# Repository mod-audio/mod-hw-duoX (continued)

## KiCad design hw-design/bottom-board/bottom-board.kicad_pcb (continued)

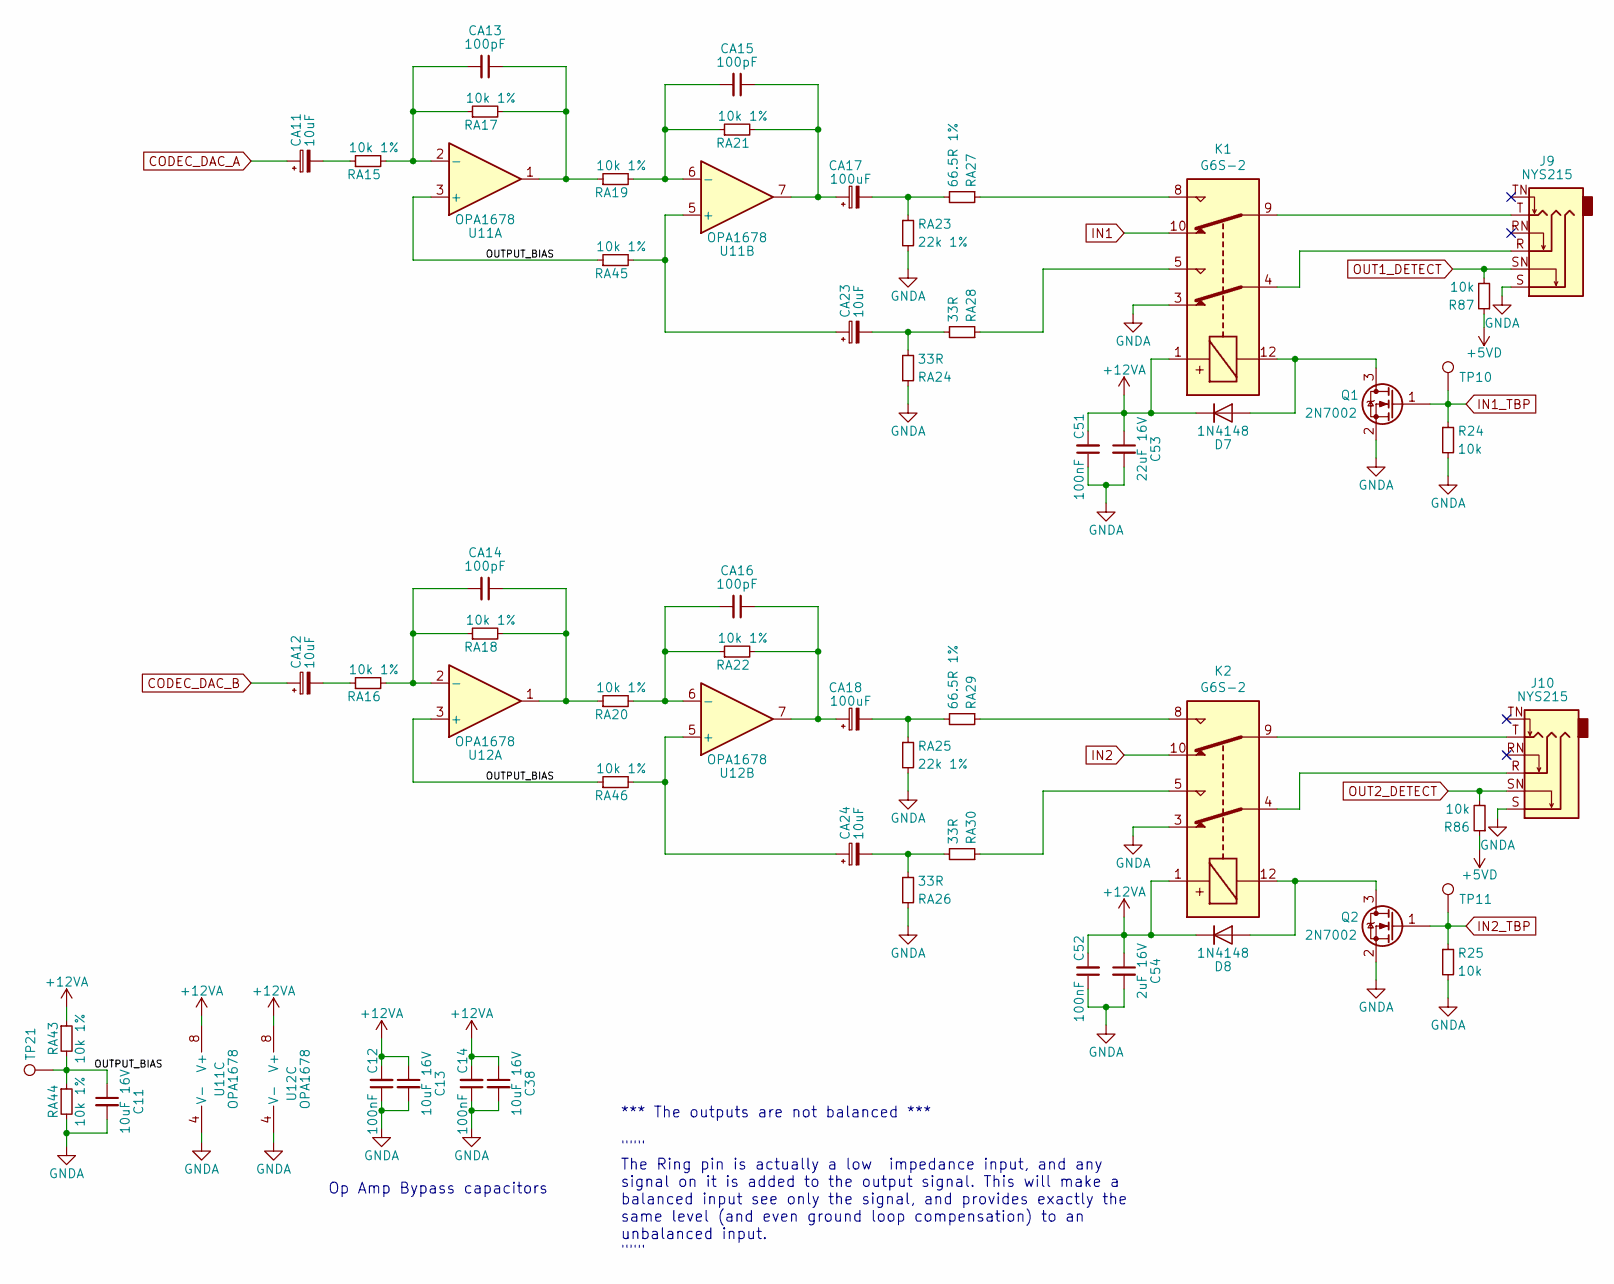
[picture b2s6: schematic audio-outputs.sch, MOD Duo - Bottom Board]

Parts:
C11, C13, C38: 10uF 16V; C_0805_2012Metric; MPN CL21A106KOFNNNE
C12, C14, C51, C52: 100nF; C_0603_1608Metric; MPN GCM188R71C104KA37D
C53: 22uF 16V; C_0805_2012Metric; MPN GRM21BC81C226ME44L
C54: 2uF 16V; C_0805_2012Metric; MPN GRM21BC81C226ME44L
CA11, CA12, CA23, CA24: 10uF; CP_Elec_4x5.7; MPN EEE-HB1C100R
CA13, CA14, CA15, CA16: 100pF; C_0603_1608Metric; MPN C0603C101J3GACTU
CA17, CA18: 100uF; CP_Elec_6.3x7.7; MPN UWX1C101MCL1GB
D7, D8: 1N4148; D_SOD-323; MPN 1N4148WX-TP
J9, J10: NYS215; NMJ6HCD2; MPN NYS215
K1, K2: G6S-2; Relay_DPDT_Omron_G6S-2F; MPN EE2-12NU-L
Q1, Q2: 2N7002; SOT-23; MPN 2N7002P,215
R24, R25, R86, R87: 10k; R_0603_1608Metric; MPN RMCF0603JT10K0
RA15, RA16, RA17, RA18, RA19, RA20, RA21, RA22, RA43, RA44, RA45, RA46: 10k 1%; R_0603_1608Metric; MPN RR0816P-103-D
RA23, RA25: 22k 1%; R_0603_1608Metric; MPN RR0816P-223-D
RA24, RA26, RA28, RA30: 33R; R_0603_1608Metric; MPN RT0603DRE0733RL
RA27, RA29: 66.5R 1%; R_0603_1608Metric; MPN RR0816Q-66R5-D-80R
TP10, TP11, TP21: TestPoint; TestPoint_Pad_D1.0mm
U11, U12: OPA1678; SOIC-8_3.9x4.9mm_P1.27mm; MPN OPA1678IDR

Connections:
+5VD: R86.1, R87.1; also elsewhere on the board
+12VA: C12.2, C13.1, C14.2, C38.1, C51.2, C52.2, C53.1, C54.1, D7.1 (K), D8.1 (K), K1.1, K2.1, RA43.1, U11.8 (V+), U12.8 (V+); also elsewhere on the board
/audio-outputs/OUTPUT_BIAS: C11.1, RA43.2, RA44.1, RA45.1, RA46.1, TP21.1, U11.3 (+), U12.3 (+)
CODEC_DAC_A: CA11.1; also elsewhere on the board
CODEC_DAC_B: CA12.1; also elsewhere on the board
IN1: K1.10; also elsewhere on the board
IN1_TBP: Q1.1 (G), R24.1, TP10.1; also elsewhere on the board
IN2: K2.10; also elsewhere on the board
IN2_TBP: Q2.1 (G), R25.1, TP11.1; also elsewhere on the board
unnamed: CA11.2, RA15.1
unnamed: CA12.2, RA16.1
unnamed: CA13.1, RA17.2, RA19.1, U11.1
unnamed: CA13.2, RA15.2, RA17.1, U11.2 (-)
unnamed: CA14.1, RA18.2, RA20.1, U12.1
unnamed: CA14.2, RA16.2, RA18.1, U12.2 (-)
unnamed: CA15.1, CA17.1, RA21.2, U11.7
unnamed: CA15.2, RA19.2, RA21.1, U11.6 (-)
unnamed: CA16.1, CA18.1, RA22.2, U12.7
unnamed: CA16.2, RA20.2, RA22.1, U12.6 (-)
unnamed: CA17.2, RA23.1, RA27.2
unnamed: CA18.2, RA25.1, RA29.2
unnamed: CA23.1, RA45.2, U11.5 (+)
unnamed: CA23.2, RA24.2, RA28.2
unnamed: CA24.1, RA46.2, U12.5 (+)
unnamed: CA24.2, RA26.2, RA30.2
unnamed: D7.2 (A), K1.12, Q1.3 (D)
unnamed: D8.2 (A), K2.12, Q2.3 (D)
unnamed: J9.R, K1.4
unnamed: J9.T, K1.9
unnamed: J10.R, K2.4
unnamed: J10.T, K2.9
unnamed: K1.5, RA28.1
unnamed: K1.8, RA27.1
unnamed: K2.5, RA30.1
unnamed: K2.8, RA29.1
OUT1_DETECT: J9.SN, R87.2; also elsewhere on the board
OUT2_DETECT: J10.SN, R86.2; also elsewhere on the board

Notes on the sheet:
*** The outputs are not balanced *** """ The Ring pin is actually a low impedance input, and any signal on it is added to the output signal. This will make a balanced input see only the signal, and provides exactly the same level (and even ground loop compensation) to an unbalanced input. """
Op Amp Bypass capacitors

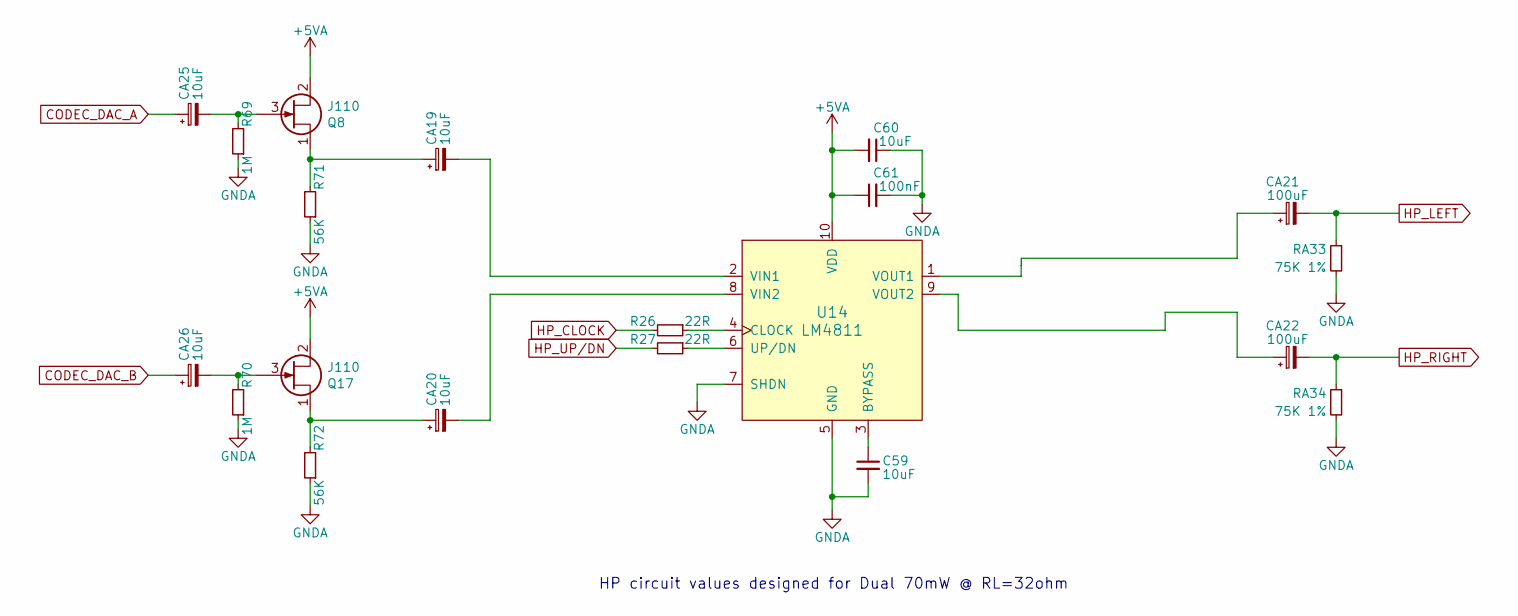
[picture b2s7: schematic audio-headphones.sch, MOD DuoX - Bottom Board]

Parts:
C59, C60: 10uF; C_0603_1608Metric; MPN CL10A106MQ8NNNC
C61: 100nF; C_0603_1608Metric; MPN GCM188R71C104KA37D
CA19, CA20, CA25, CA26: 10uF; CP_Elec_4x5.7; MPN EEE-HB1C100R
CA21, CA22: 100uF; CP_Elec_6.3x7.7; MPN UWX1C101MCL1GB
Q8, Q17: J110; SOT-23; MPN PMBFJ110,215
R26, R27: 22R; R_0603_1608Metric; MPN RMCF0603JT22R0
R69, R70: 1M; R_0603_1608Metric; MPN RT0603BRD071ML
R71, R72: 56K; R_0603_1608Metric; MPN RMCF0603FT56K0
RA33, RA34: 75K 1%; R_0603_1608Metric; MPN RR0816P-753-D
U14: LM4811; MSOP-10_3x3mm_P0.5mm; MPN LM4811MM/NOPB

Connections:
CODEC_DAC_A: CA25.1; also elsewhere on the board
CODEC_DAC_B: CA26.1; also elsewhere on the board
HP_CLOCK: R26.2; also elsewhere on the board
HP_LEFT: CA21.2, RA33.1; also elsewhere on the board
HP_RIGHT: CA22.2, RA34.1; also elsewhere on the board
HP_UP/DN: R27.2; also elsewhere on the board
unnamed: C59.1, U14.3 (BYPASS)
unnamed: CA19.1, Q8.1 (D), R71.2
unnamed: CA19.2, U14.2 (VIN1)
unnamed: CA20.1, Q17.1 (D), R72.2
unnamed: CA20.2, U14.8 (VIN2)
unnamed: CA21.1, U14.1 (VOUT1)
unnamed: CA22.1, U14.9 (VOUT2)
unnamed: CA25.2, Q8.3 (G), R69.2
unnamed: CA26.2, Q17.3 (G), R70.2
unnamed: R26.1, U14.4 (CLOCK)
unnamed: R27.1, U14.6 (UP/DN)

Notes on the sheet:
HP circuit values designed for Dual 70mW @ RL=32ohm

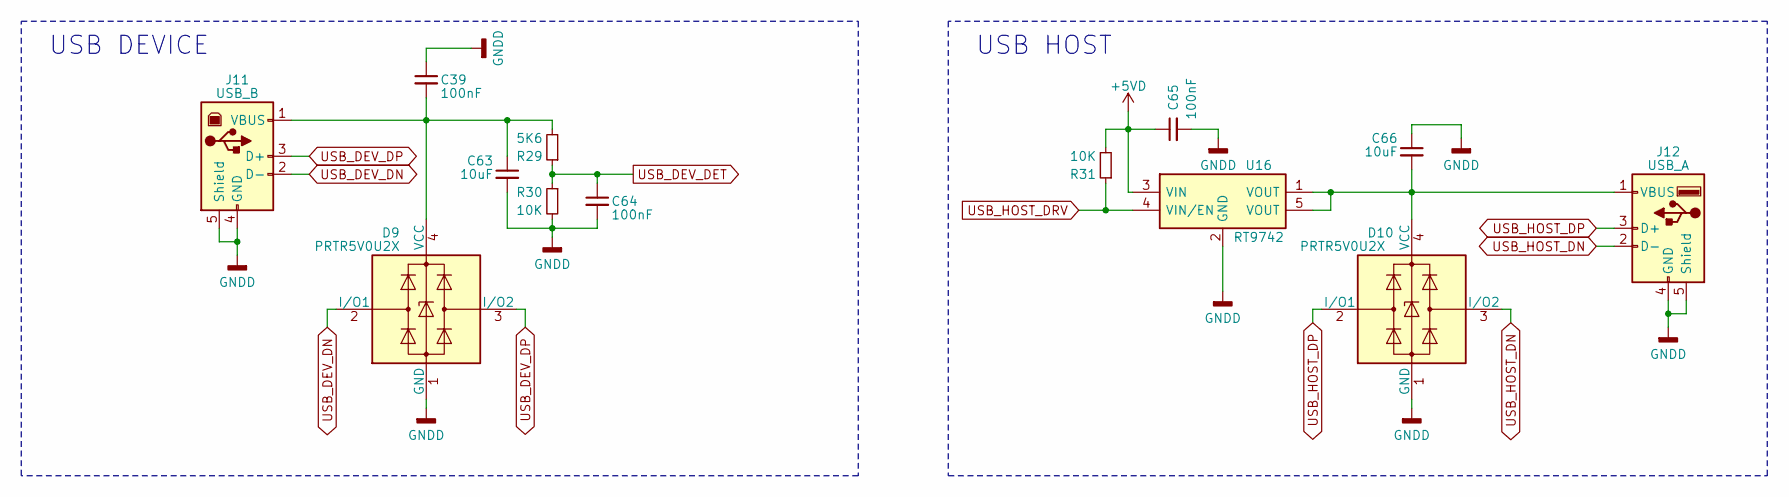
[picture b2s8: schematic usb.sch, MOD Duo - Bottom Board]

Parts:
C39, C64, C65: 100nF; C_0603_1608Metric; MPN GCM188R71C104KA37D
C63, C66: 10uF; C_0603_1608Metric; MPN CL10A106MQ8NNNC
D9, D10: PRTR5V0U2X; SOT-143; MPN PRTR5V0U2X,215
J11: USB_B; USB_B_OST_USB-B1HSxx_Horizontal; MPN 61729-1011BLF
J12: USB_A; USB_A_Vertical; MPN 73725-0110BLF
R29: 5K6; R_0603_1608Metric; MPN ERA-3AEB5621V
R30, R31: 10K; R_0603_1608Metric; MPN RR0816P-103-D
U16: RT9742; TSOT-23-5; MPN RT9742MNGJ5

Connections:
+5VD: C65.1, R31.2, U16.3 (VIN); also elsewhere on the board
unnamed: C39.2, C63.1, D9.4 (VCC), J11.1 (VBUS), R29.2
unnamed: C66.2, D10.4 (VCC), J12.1 (VBUS), U16.1 (VOUT), U16.5 (VOUT)
USB_DEV_DET: C64.1, R29.1, R30.1; also elsewhere on the board
USB_DEV_DN: D9.2 (I/O1), J11.2 (D-); also elsewhere on the board
USB_DEV_DP: D9.3 (I/O2), J11.3 (D+); also elsewhere on the board
USB_HOST_DN: D10.3 (I/O2), J12.2 (D-); also elsewhere on the board
USB_HOST_DP: D10.2 (I/O1), J12.3 (D+); also elsewhere on the board
USB_HOST_DRV: R31.1, U16.4 (VIN/EN); also elsewhere on the board

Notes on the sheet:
USB DEVICE
USB HOST

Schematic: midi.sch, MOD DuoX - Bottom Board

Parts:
D11, D12: 1N4148; D_SOD-323; MPN 1N4148WX-TP
J13, J14: DIN_5; SDS-50J; MPN SDS-50J
Q3, Q4: 2N7002; SOT-23; MPN 2N7002P,215
R32, R33, R34: 220R; R_0603_1608Metric; MPN ESR03EZPJ221
R35, R36: 10K; R_0603_1608Metric; MPN RR0816P-103-D
U17: 6N136S; SMDIP-8_W9.53mm; MPN 6N136S

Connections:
+5VD: R33.2, R35.1, R36.1, U17.8; also elsewhere on the board
CLI_UART_RX: J14.3; also elsewhere on the board
CLI_UART_TX: J14.1; also elsewhere on the board
MIDI_UART_RX: D12.2 (A); also elsewhere on the board
MIDI_UART_TX: Q4.1 (G); also elsewhere on the board
unnamed: D11.1 (K), R32.2, U17.2
unnamed: D11.2 (A), J13.5, U17.3
unnamed: D12.1 (K), U17.6
unnamed: J13.4, R32.1
unnamed: J14.4, R33.1
unnamed: J14.5, R34.1
unnamed: Q3.1 (G), Q4.3 (D), R36.2
unnamed: Q3.3 (D), R34.2, R35.2

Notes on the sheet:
MIDI IN
MIDI OUT
MIDI Out connector exposes the debug serial.
Opto: If = 16mA, Vf = 1.4V
MIDI In connector can be used to trigger a special boot mode by connecting pin 3 to GND.

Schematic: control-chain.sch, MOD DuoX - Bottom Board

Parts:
C67, C68: 10uF; C_0603_1608Metric; MPN CL10A106MQ8NNNC
C69: 10uF 16V; C_0805_2012Metric; MPN CL21A106KOFNNNE
C70, C71: 100nF; C_0603_1608Metric; MPN GCM188R71C104KA37D
J15: RJHSE-5381; RJ45_Amphenol_RJHSE538X; MPN RJHSE-5381
Q5, Q6: BSS84; SOT-23; MPN BSS84-7-F
R37, R38: 22R; R_0603_1608Metric; MPN RMCF0603JT22R0
R39, R40: 10K; R_0603_1608Metric; MPN RR0816P-103-D
R41, R42: 220R; R_0603_1608Metric; MPN ESR03EZPJ221
R43, R44, R45, R46: 56R; R_0603_1608Metric; MPN RMCF0603JT56R0
R47: 100R; R_0603_1608Metric; MPN RR0816P-101-D
U18: ISL83086E; SOIC-14_3.9x8.7mm_P1.27mm; MPN ISL83086EIBZ

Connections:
+5VD: C71.1, Q5.2 (S), Q6.2 (S), R39.1, U18.13 (VCC), U18.14 (VCC); also elsewhere on the board
+12V: C69.1, C70.1, J15.4, J15.5; also elsewhere on the board
CHAIN_UART_DE: R40.1, U18.4 (DE); also elsewhere on the board
CHAIN_UART_RE: R39.2, U18.3 (~RE); also elsewhere on the board
CHAIN_UART_RX: Q6.1 (G), R38.1; also elsewhere on the board
CHAIN_UART_TX: R37.1; also elsewhere on the board
unnamed: J15.10, R42.1
unnamed: J15.12, R41.1
unnamed: Q5.1 (G), R37.2, U18.5 (DI)
unnamed: R38.2, U18.2 (RO)
unnamed: R43.2, U18.12 (A)
unnamed: R44.2, U18.11 (~B)
unnamed: R45.2, U18.9 (Y)
unnamed: R46.2, U18.10 (~Z~)
RS485_RX+: J15.3, R43.1, R47.1
RS485_RX-: J15.6, R44.1, R47.2
RS485_RX_LED: C68.1, Q6.3 (D), R41.2
RS485_TX+: J15.1, R45.1
RS485_TX-: J15.2, R46.1
RS485_TX_LED: C67.1, Q5.3 (D), R42.2

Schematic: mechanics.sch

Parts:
FID1, FID2, FID3: FIDUCIAL; fiducial_in-circuit
H1, H2, H3, H4, H5: HOLE; Hole_3.5mm
H6, H7: Standoff; 9774027151R; MPN 9774027151R
IMG1: Logo; mod-logo

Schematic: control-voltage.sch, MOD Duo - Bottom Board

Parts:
C34: 10uF 16V; C_0805_2012Metric; MPN CL21A106KOFNNNE
C35, C76, C81: 10uF; C_0603_1608Metric; MPN CL10A106MQ8NNNC
C73, C74: 33nF; C_0603_1608Metric; MPN C0603C333K4RACTU
C75, C80, C82, C83: 100nF; C_0603_1608Metric; MPN GCM188R71C104KA37D
C77: 1uF; C_0603_1608Metric; MPN CL10B105KP8NNNC
D13, D20: 1N4148WS-Diode; D_SOD-323
D14, D15: BAT54S; SOT-23; MPN BAT54SFILM
J16, J17: NYS215; NMJ6HCD2; MPN NYS215
R17, R48, R50, R51, R52, R79, R80, R82: 10K; R_0603_1608Metric; MPN RR0816P-103-D
RA31, RA32, RA35, RA36, RA47, RA48, RA51, RA52: 10K 1%; R_0603_1608Metric; MPN RR0816P-103-D
RA49, RA50: 499k 1%; R_0603_1608Metric; MPN ERJ-3EKF4993V
RA53, RA54: 1K 1%; R_0603_1608Metric; MPN CR0603-FX-3012ELF
TP14, TP15, TP16: TestPoint; TestPoint_Pad_D1.0mm
U4: LD1117S50TR_SOT223; SOT-223-3_TabPin2; MPN LD1117S50TR
U9, U13: DG9426E; TSSOP-16_4.4x5mm_P0.65mm
U10: LM358; TSSOP-8_3x3mm_P0.65mm; MPN LM358DGKR
U20: ADC122S021; VSSOP-8_3.0x3.0mm_P0.65mm; MPN ADC122S021CIMM/NOPB
U21: MIC2076A; SOIC-8_3.9x4.9mm_P1.27mm; MPN MIC2076A-1YM
U22: 74LVC3G17; VSSOP-8_2.3x2mm_P0.5mm; MPN SN74LVC3G17DCUR
U24: MCP4922-EP; SOIC-14_3.9x8.7mm_P1.27mm; MPN MCP4922T-E/SL

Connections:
+5VP: C35.1, C75.2, C76.1, C77.2, D14.2, D15.2, R82.1, U4.2 (VO), U9.12 (VL), U20.2 (VA), U21.7 (IN)
+12VA: C34.1, U4.3 (VI), U9.13 (V+), U10.8 (V+), U13.13 (V+); also elsewhere on the board
CV_10V_OUT1: RA51.2, U10.1, U13.11
CV_10V_OUT2: RA52.2, U10.7, U13.15
CV_ADC_DIN: U20.6 (DIN); also elsewhere on the board
CV_ADC_DOUT: U20.7 (DOUT); also elsewhere on the board
CV_ADC_SCLK: U20.8 (SCLK); also elsewhere on the board
CV_ADC_~CS~: TP16.1, U20.1 (~CS~); also elsewhere on the board
CV_DAC_SCK: U22.3; also elsewhere on the board
CV_DAC_SDI: U22.1; also elsewhere on the board
CV_DAC_~CS~: U22.6; also elsewhere on the board
CV_EXP_SW: D13.1 (K), D20.1 (K), R48.1, U9.1, U9.8, U9.9, U9.16
CV_IN_DET: J16.SN, R82.2; also elsewhere on the board
CV_OUT_1: RA53.2, U10.3 (+)
CV_OUT_2: RA54.2, U10.5 (+)
CV_OUT_DET: J17.SN, R17.2; also elsewhere on the board
EXP_FLAG1: R80.1, U21.2 (FLGA); also elsewhere on the board
EXP_FLAG2: R79.1, U21.3 (FLGB); also elsewhere on the board
HP_CV_JACK_RING: J17.R, U13.6, U13.14
HP_CV_JACK_TIP: J17.T, U13.3, U13.10
HP_DISABLE: R52.1, U13.1, U13.8, U13.9, U13.16; also elsewhere on the board
HP_LEFT: U13.2; also elsewhere on the board
HP_RIGHT: U13.7; also elsewhere on the board
unnamed: C73.1, D15.3, U9.2, U9.15, U20.5 (IN1)
unnamed: C74.1, D14.3, U9.7, U9.10, U20.4 (IN2)
unnamed: RA31.2, RA32.1, U9.6
unnamed: RA35.2, RA36.1, U9.3
unnamed: RA47.2, RA51.1, U10.2 (-)
unnamed: RA48.2, RA52.1, U10.6 (-)
unnamed: RA49.2, RA53.1, U24.14 (VoutA)
unnamed: RA50.2, RA54.1, U24.10 (VoutB)
unnamed: U22.2, U24.3 (~CS~)
unnamed: U22.5, U24.4 (SCK)
unnamed: U22.7, U24.5 (SDI)

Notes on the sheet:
CV INPUT
CV OUTPUT
Exp. Pedal Enable
MIC2076A outputs have Hi-Z when disabled
DAC outputs have Hi-Z (500k) when shutdown is on
Amplify the signel by a factor of 2, to scale back to the 0 to 10V range

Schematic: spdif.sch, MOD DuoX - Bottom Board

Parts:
C84: 10nF; C_0603_1608Metric; MPN CL10B103KA8NNNC
C85: 22pF; C_0603_1608Metric; MPN C0603C220K4GACTU
J18: MJ-3536N; MPN MJ-3536N
R55: 243R; R_0603_1608Metric; MPN RC0603FR-07243RL
R56: 107R; R_0603_1608Metric; MPN RC0603FR-07107RL
TR1: Transformer_1P_1S_SO8; PE-65812NL; MPN PE-65812NL

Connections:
CODEC_SPDIF_OUT: C84.2; also elsewhere on the board
unnamed: C84.1, R55.2
unnamed: C85.2, J18.S, TR1.5 (SA)
unnamed: J18.T, TR1.8 (SB)
unnamed: R55.1, R56.1, TR1.1 (AA)

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
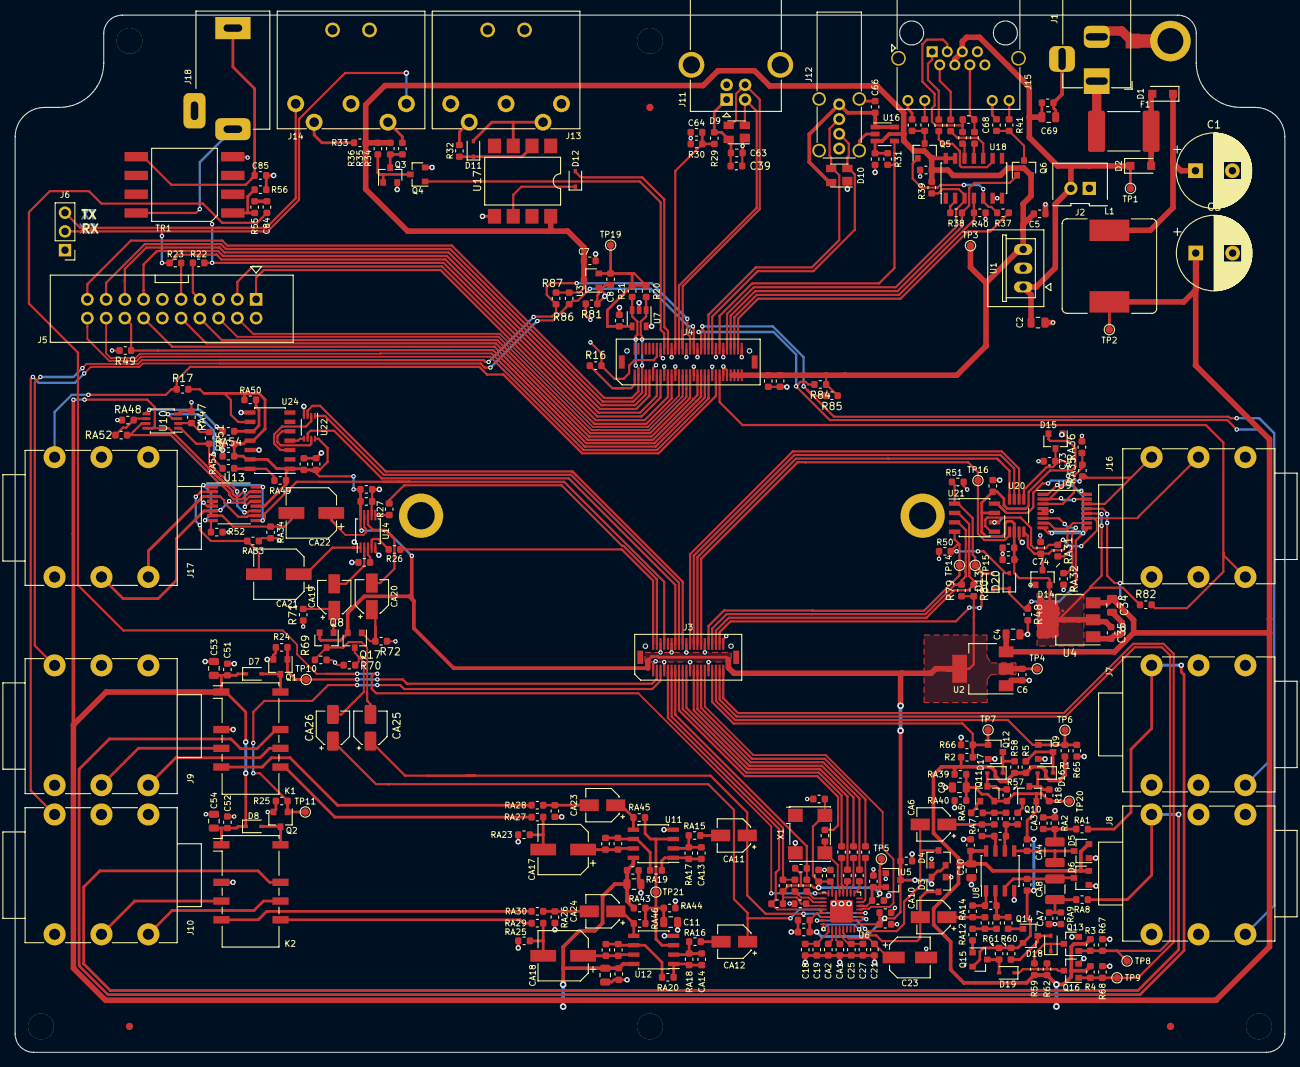
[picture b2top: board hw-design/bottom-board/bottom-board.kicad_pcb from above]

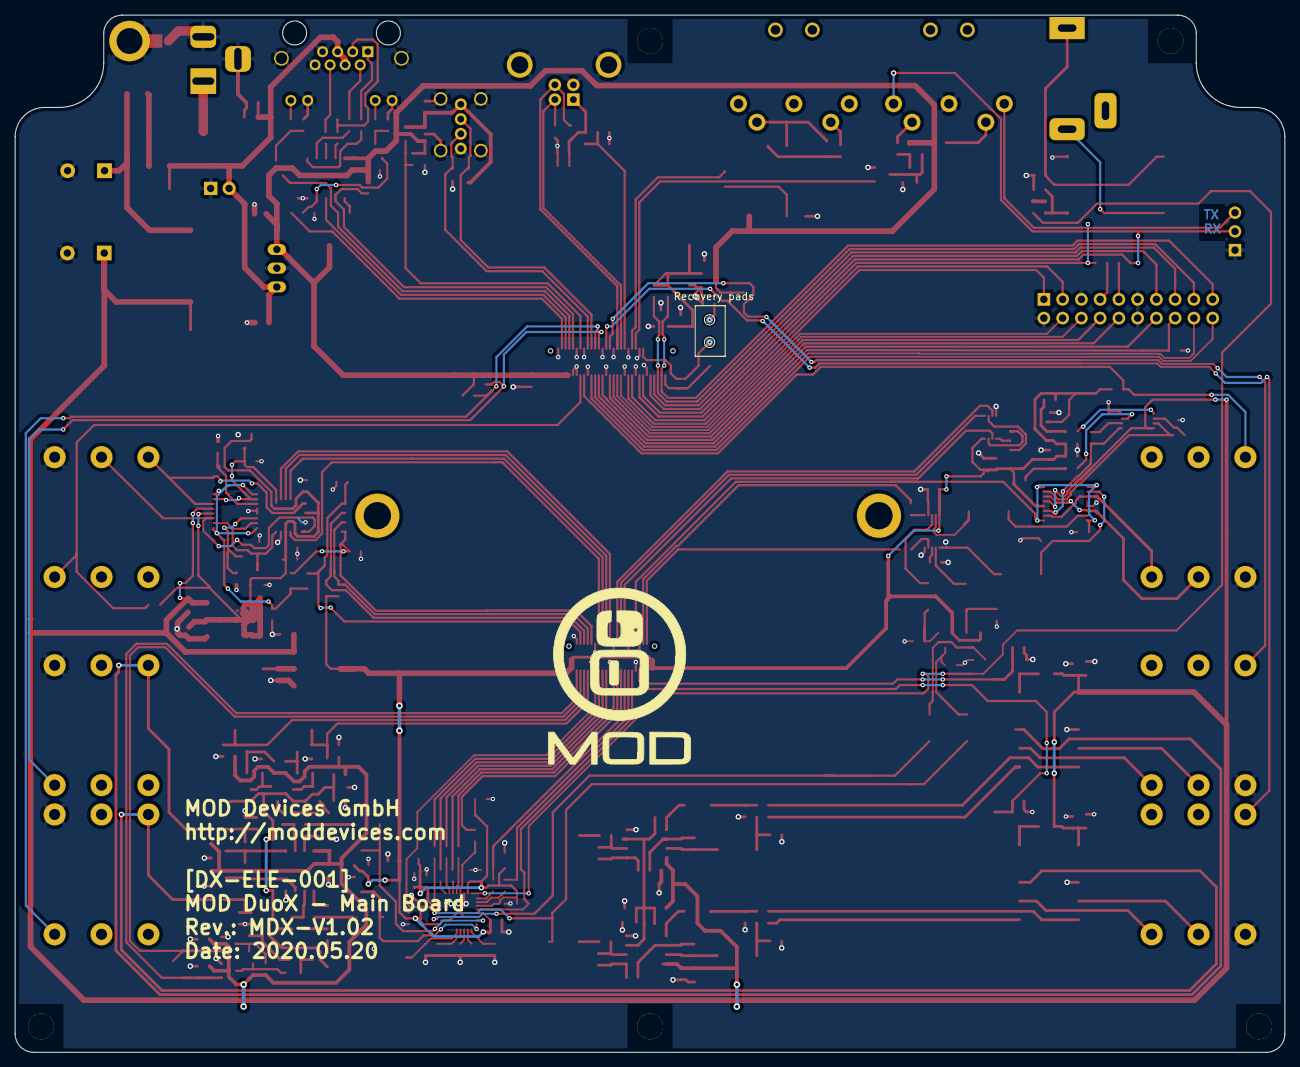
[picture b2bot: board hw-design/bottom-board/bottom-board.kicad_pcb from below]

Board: 2 copper layers, 172.0 x 140.5 mm, 331 parts (3 on the bottom side), 213 nets.

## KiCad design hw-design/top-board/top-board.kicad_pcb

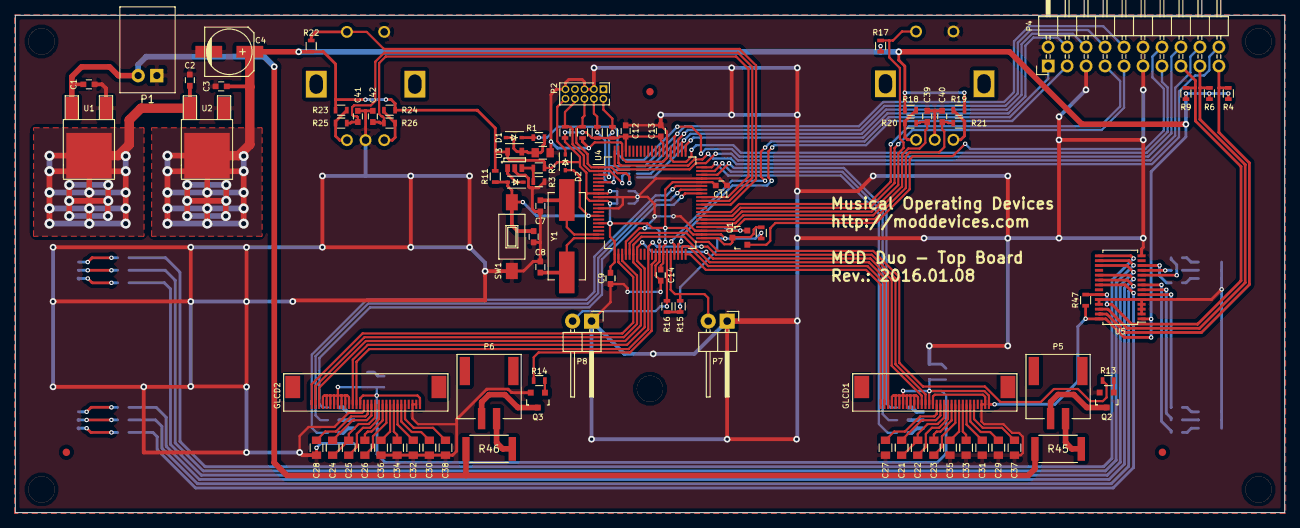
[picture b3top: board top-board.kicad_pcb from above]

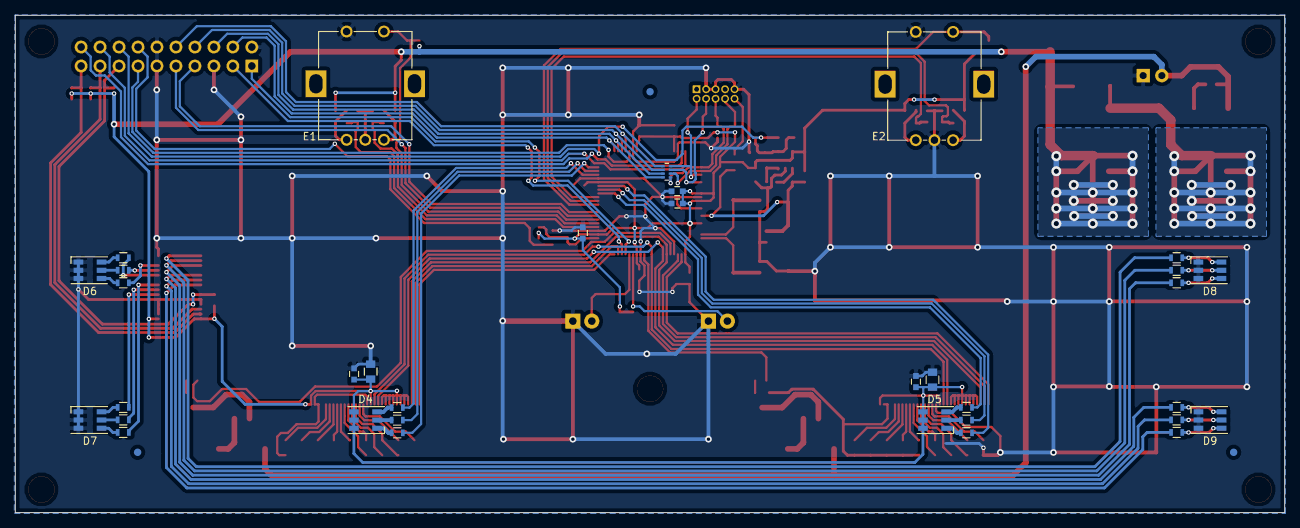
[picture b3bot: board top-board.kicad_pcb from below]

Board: 2 copper layers, 170.0 x 66.6 mm, 131 parts (37 on the bottom side), 117 nets.

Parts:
C1, C2, C3, C6, C9, C10, C11, C12, C13, C14, C15, C16, C17, C18: 100nF; C_0603
C4: 100uF; c_elec_6.3x5.3
C5, C19, C20: 10uF; C_0805
C7, C8: 39pF; C_0603
C21, C22, C23, C24, C25, C26, C27, C28, C29, C30, C31, C32, C33, C34, C35, C36, C37, C38: 1uF; C_0805
C39, C40, C41, C42: 0.01uF; C_0603
D1, D2, D3: 1N4148; SOD-323
D4, D5, D6, D7, D8, D9: LED_RGB; LED_RGB_PLLC-6
E1, E2: PEC11R; PEC11R-4xxxF-Sxxxx
FID1, FID2, FID3, FID4, FID5, FID6: FIDUCIAL; fiducial_in-circuit
GLCD1, GLCD2: ERC12864-2; ER-CON30HB-1
H1, H2, H3, H4, H5: HOLE; Hole_3.5mm
P1: POWER_CONN; S2B-XH-A
P2: ISP; Pin_Header_Straight_2x05_Pitch1.27mm
P4: BOTTOM_CONN; Pin_Header_Angled_2x10
P5, P6: BACKLIGHT; SMD_Pin_Header_Angled_2x01_Pitch2.00mm
P7, P8: FOOTSWITCH; Pin_Header_Angled_1x02
Q1: 2N7002; SOT-23
Q2, Q3: MMBT2222A; SOT-23
R1: 160K; R_0603
R2, R3, R5, R7, R8, R10, R11, R12, R15, R16, R17, R18, R19, R20, R21, R22, R23, R24, R25, R26, R47: 10K; R_0603
R4, R6, R9: 100K; R_0603
R13, R14: 3K3; R_0603
R27, R28, R29, R30, R31, R32, R33, R34, R35, R36, R37, R38, R39, R40, R41, R42, R43, R44: 220R; R_0603
R45, R46: 120R; R_2512
RP1: R_PACK4; R_Array_Concave_4x0402
SW1: BT_RESET; SW_SPST_FSMSM
U1: NCP1117DT50G; DPAK-2
U2: NCP1117DT33G; DPAK-2
U3: MCP6001; SOT-23-5
U4: LPC1759FBD80; LQFP-80_12x12mm_Pitch0.5mm
U5: PCA9685; TSSOP-28_4.4x9.7mm_Pitch0.65mm
Y1: 10MHz; Crystal_HC49-SD_SMD

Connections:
+3V3: C3.1, C4.1, C9.1, C10.1, C11.1, C12.1, C13.1, C14.1, C15.1, C16.1, C17.2, C18.2, C19.2, C20.2, D4.4, D4.5, D4.6, D5.4, D5.5, D5.6, GLCD1.1, GLCD1.17, GLCD1.20, GLCD1.21, GLCD1.22, GLCD1.23, GLCD1.24, GLCD1.25, GLCD1.26, GLCD1.27, GLCD2.1, GLCD2.17, GLCD2.20, GLCD2.21, GLCD2.22, GLCD2.23, GLCD2.24, GLCD2.25, GLCD2.26, GLCD2.27, R2.1, R4.1, R5.1, R6.1, R7.1, R8.1, R9.1, R11.1, R12.1, R15.1, R16.1, R17.1, R18.1, R19.1, R22.1, R23.1, R24.1, R47.2, U2.2, U3.5, U4.8, U4.10, U4.16, U4.21, U4.34, U4.42, U4.56, U4.67, U4.77, U5.1, U5.28
+12V: C1.1, P1.2, R45.2, R46.2, U1.3
CLI_UART_RX: P4.9, U4.47
CLI_UART_TX: P4.7, U4.48
ENC1_A: C40.1, R21.1, U4.44
ENC1_B: C39.1, R20.1, U4.45
ENC1_SW: E1.2, R17.2, U4.46
ENC2_A: C42.1, R26.1, U4.52
ENC2_B: C41.1, R25.1, U4.51
ENC2_SW: E2.2, R22.2, U4.50
FS1: P7.2, R15.2, U4.36
FS1_LED_B: R27.2, U4.60
FS1_LED_G: R29.2, U4.58
FS1_LED_R: R28.2, U4.59
FS2: P8.2, R16.2, U4.35
FS2_LED_B: R30.2, U4.55
FS2_LED_G: R32.2, U4.53
FS2_LED_R: R31.2, U4.54
GLCD1_BL: R13.1, U4.25
GLCD1_CS: GLCD1.30, U4.40
GLCD1_RESET: GLCD1.29, U4.39
GLCD2_BL: R14.1, U4.32
GLCD2_CS: GLCD2.30, U4.22
GLCD2_RESET: GLCD2.29, U4.23
GLCD_A0: GLCD1.28, GLCD2.28, U4.26
GLCD_SCL: GLCD1.19, GLCD2.19, U4.27
GLCD_SI: GLCD1.18, GLCD2.18, U4.30
GNDD: C1.2, C2.2, C3.2, C4.2, C5.1, C6.2, C7.2, C8.2, C9.2, C10.2, C11.2, C12.2, C13.2, C14.2, C15.2, C16.2, C17.1, C18.1, C19.1, C20.1, C27.1, C28.1, C29.1, C30.1, C31.1, C32.1, C33.1, C34.1, C35.1, C36.1, C37.1, C38.1, C39.2, C40.2, C41.2, C42.2, D6.1, D6.2, D6.3, D7.1, D7.2, D7.3, D8.1, D8.2, D8.3, D9.1, D9.2, D9.3, E1.1, E1.4, E2.1, E2.4, GLCD1.2, GLCD1.3, GLCD1.16, GLCD2.2, GLCD2.3, GLCD2.16, P1.1, P2.3, P2.5, P2.9, P4.2, P4.5, P4.11, P4.12, P7.1, P8.1, Q1.2, Q2.2, Q3.2, R3.2, R10.1, SW1.2, U1.1, U2.1, U3.2, U4.9, U4.12, U4.24, U4.33, U4.43, U4.57, U4.66, U4.78, U5.2, U5.3, U5.4, U5.5, U5.14, U5.24, U5.25
HMI_ISP_ENABLE: P4.14, Q1.1
HMI_RESET: D1.1, P4.16, R1.2
HMI_RFU_01(RX): P4.1, U4.37
HMI_RFU_02(TX): P4.3, U4.38
HMI_UART_RX: P4.20, U4.79
HMI_UART_TX: P4.18, U4.80
JTAG_RESET: C6.1, D2.2, D3.2, R11.2, SW1.1, U4.14
JTAG_TCK_SWDCLK: P2.4, R7.2, RP1.7, U4.5
JTAG_TDI: P2.8, R8.2, RP1.6, U4.2
JTAG_TDO_SWO: P2.6, R10.2, RP1.5, U4.1
JTAG_TMS_SDWIO: P2.2, R5.2, RP1.8, U4.3
unnamed: C2.1, U1.2, U2.3
unnamed: C5.2, D1.2, R1.1, U3.4
unnamed: C7.1, U4.19, Y1.1
unnamed: C8.1, U4.20, Y1.2
unnamed: C21.1, GLCD1.14
unnamed: C21.2, C22.2, GLCD1.13
unnamed: C22.1, GLCD1.12
unnamed: C23.1, GLCD1.10
unnamed: C23.2, GLCD1.11
unnamed: C24.1, GLCD2.14
unnamed: C24.2, C25.2, GLCD2.13
unnamed: C25.1, GLCD2.12
unnamed: C26.1, GLCD2.10
unnamed: C26.2, GLCD2.11
unnamed: C27.2, GLCD1.15
unnamed: C28.2, GLCD2.15
unnamed: C29.2, GLCD1.6
unnamed: C30.2, GLCD2.6
unnamed: C31.2, GLCD1.7
unnamed: C32.2, GLCD2.7
unnamed: C33.2, GLCD1.8
unnamed: C34.2, GLCD2.8
unnamed: C35.2, GLCD1.9
unnamed: C36.2, GLCD2.9
unnamed: C37.2, GLCD1.5
unnamed: C38.2, GLCD2.5
unnamed: D2.1, P2.10
unnamed: D3.1, U3.1
unnamed: D4.1, R27.1
unnamed: D4.2, R28.1
unnamed: D4.3, R29.1
unnamed: D5.1, R30.1
unnamed: D5.2, R31.1
unnamed: D5.3, R32.1
unnamed: D6.4, R33.1
unnamed: D6.5, R34.1
unnamed: D6.6, R35.1
unnamed: D7.4, R36.1
unnamed: D7.5, R37.1
unnamed: D7.6, R38.1
unnamed: D8.4, R41.1
unnamed: D8.5, R40.1
unnamed: D8.6, R39.1
unnamed: D9.4, R44.1
unnamed: D9.5, R43.1
unnamed: D9.6, R42.1
unnamed: E1.3, R19.2, R21.2
unnamed: E1.5, R18.2, R20.2
unnamed: E2.3, R24.2, R26.2
unnamed: E2.5, R23.2, R25.2
unnamed: P5.1, Q2.3
unnamed: P5.2, R45.1
unnamed: P6.1, Q3.3
unnamed: P6.2, R46.1
unnamed: Q1.3, R12.2, U4.41
unnamed: Q2.1, R13.2
unnamed: Q3.1, R14.2
unnamed: R2.2, R3.1, U3.3
unnamed: R33.2, U5.12
unnamed: R34.2, U5.11
unnamed: R35.2, U5.10
unnamed: R36.2, U5.8
unnamed: R37.2, U5.7
unnamed: R38.2, U5.6
unnamed: R39.2, U5.15
unnamed: R40.2, U5.16
unnamed: R41.2, U5.17
unnamed: R42.2, U5.19
unnamed: R43.2, U5.20
unnamed: R44.2, U5.21
PM_LEDS_OE: P4.15, R9.2, R47.1, U5.23
PM_LEDS_SCL: P4.17, R6.2, U5.26
PM_LEDS_SDA: P4.19, R4.2, U5.27
POWER_BUTTON: P4.13, U4.65
SPI0_CLK_HMI: P4.8, RP1.2, U4.63
SPI0_CS0_HMI: P4.10, RP1.1, U4.64
SPI0_MISO_HMI: P4.4, RP1.4, U4.61
SPI0_MOSI_HMI: P4.6, RP1.3, U4.62

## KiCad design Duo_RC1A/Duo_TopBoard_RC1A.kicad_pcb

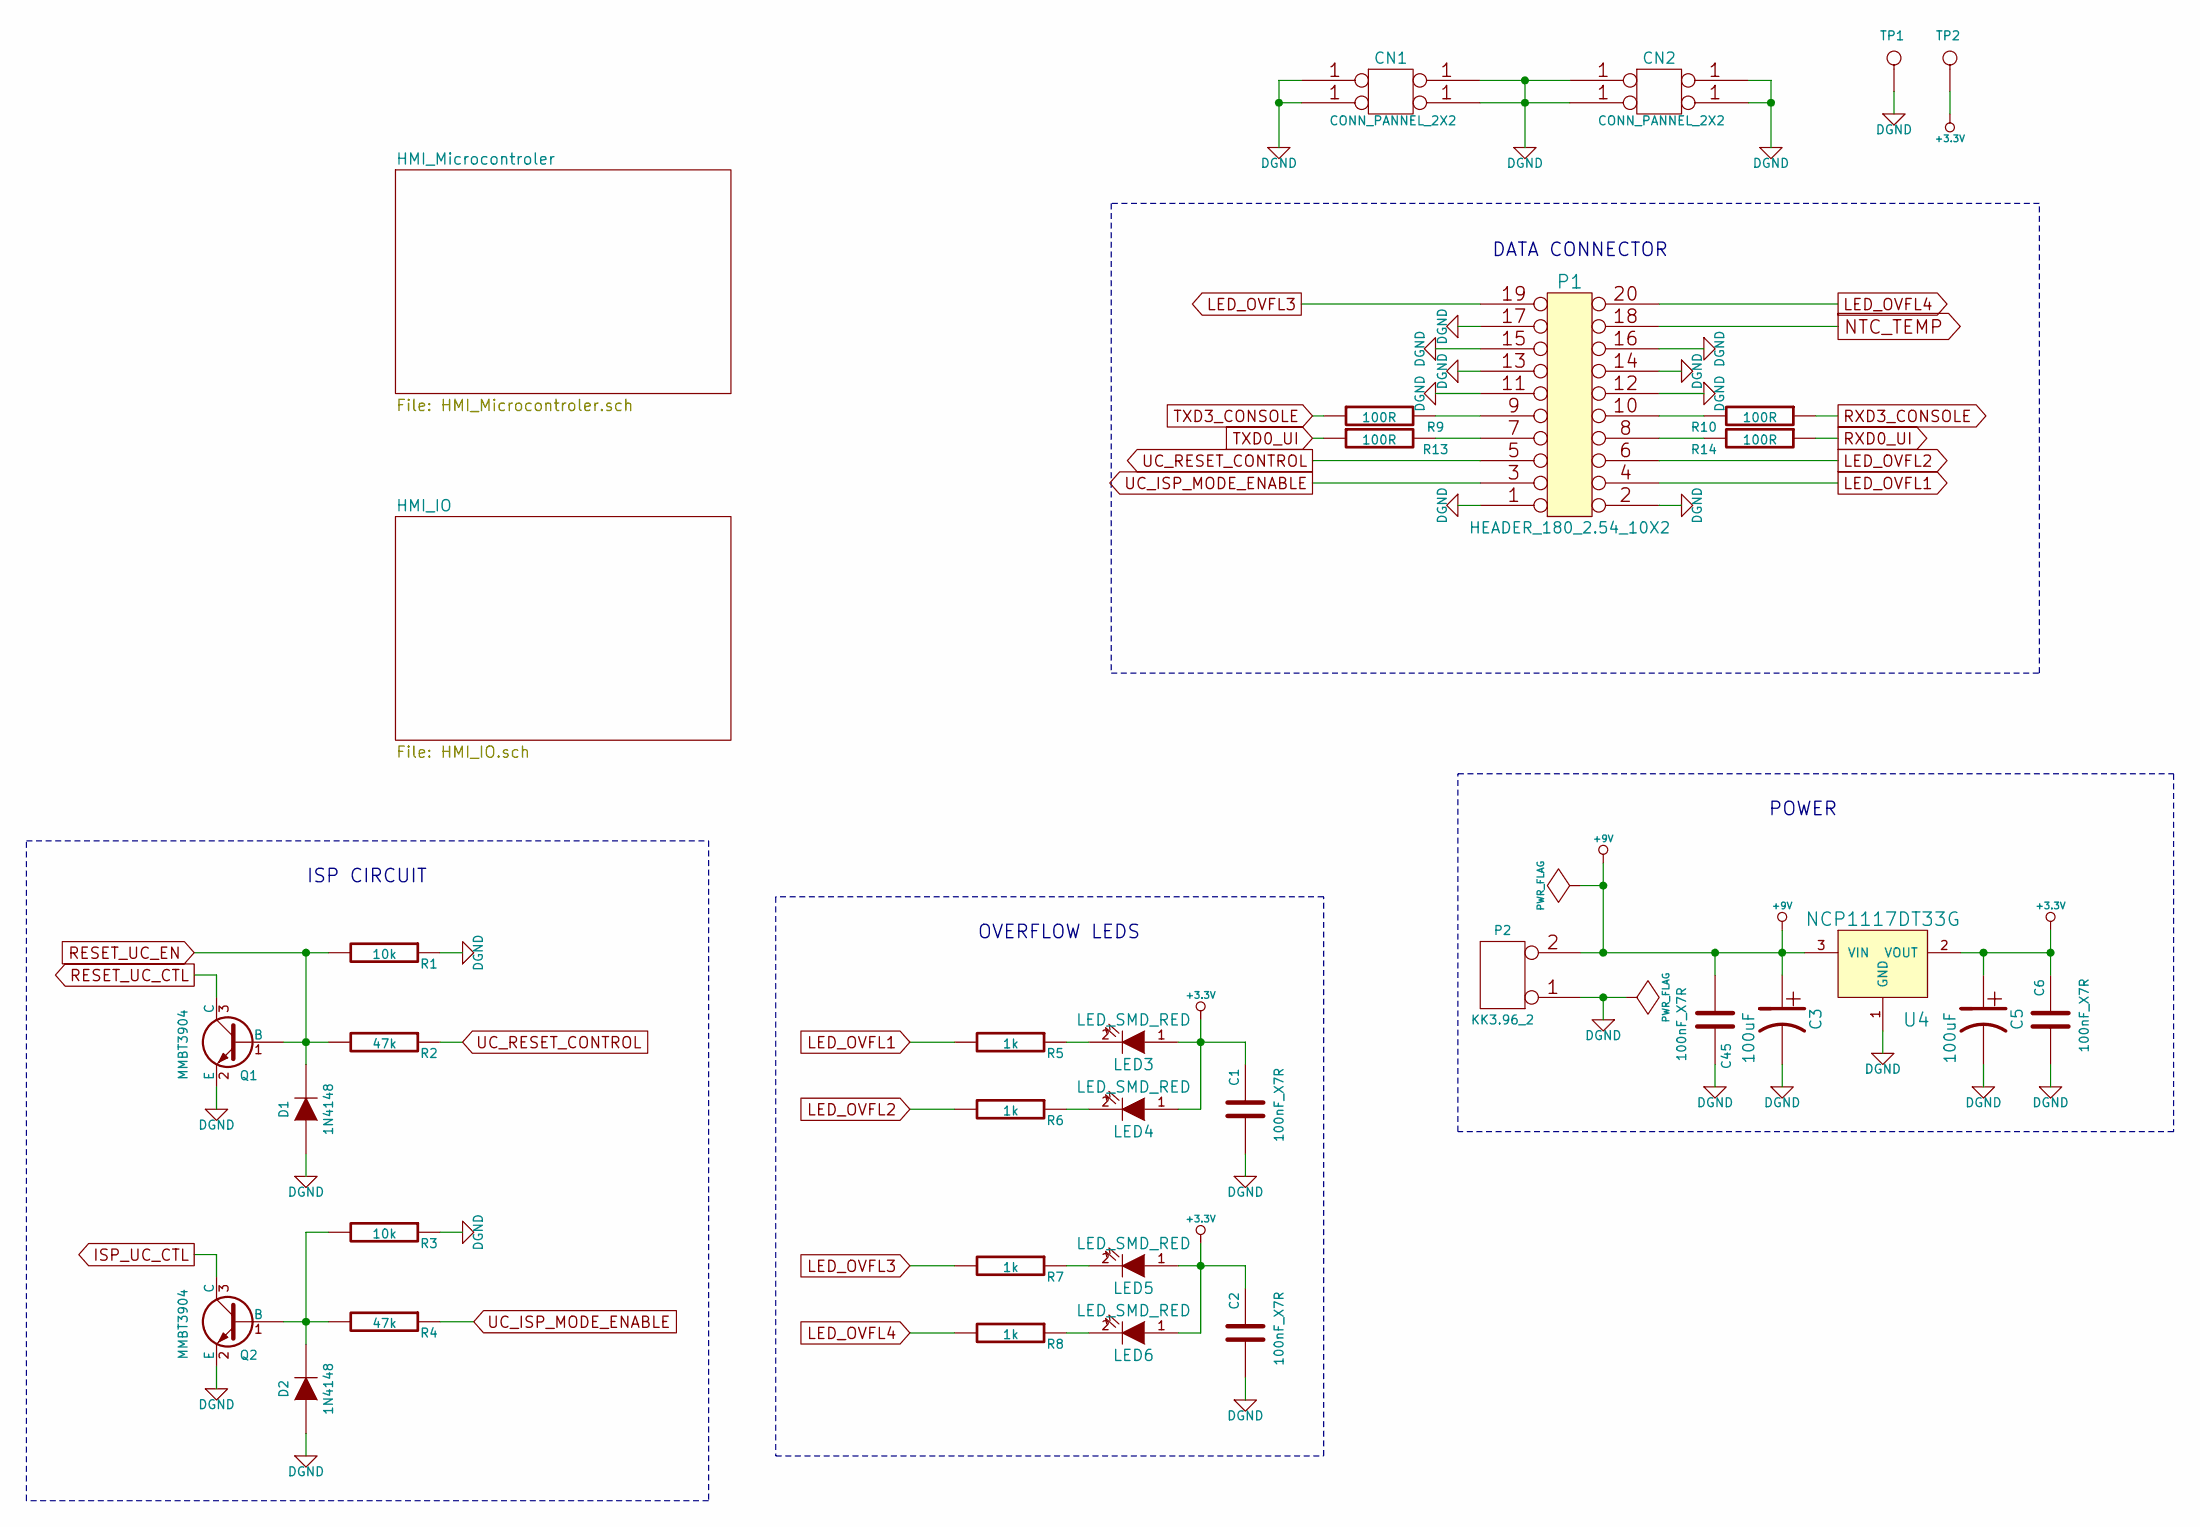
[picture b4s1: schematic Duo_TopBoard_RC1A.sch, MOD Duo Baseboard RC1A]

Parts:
C1, C2, C6, C45: 100nF_X7R; SM0603
C3, C5: 100uF; Capacitor5x11RM2
CN1, CN2: CONN_PANNEL_2X2; CONN_PANNEL
D1, D2: 1N4148; SOD323
LED3, LED4, LED5, LED6: LED_SMD_RED; SM0805
P1: HEADER_180_2.54_10X2; Pin_Header_180_2.54_2x10
P2: KK3.96_2; KK3.96_2PIN
Q1, Q2: MMBT3904; SOT23
R1, R3: 10k; SM0603
R2, R4: 47k; SM0603
R5, R6, R7, R8: 1k; SM0603
R9, R10, R13, R14: 100R; SM0603
TP1: CONN_1; TESTPOINT_2.2MM
TP2: CONN_1; TESTPOINT_1MM
U4: NCP1117DT33G; DPAK(369C)

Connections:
+3.3V: C1.1, C2.1, C5.1, C6.1, LED3.1 (A), LED4.1 (A), LED5.1 (A), LED6.1 (A), TP2.1, U4.2 (VOUT); also elsewhere on the board
+9V: C3.1, C45.2, P2.2 (PM), U4.3 (VIN)
DGND: C1.2, C2.2, C3.2, C5.2, C6.2, C45.1, CN1.1, CN2.1, D1.1 (A), D2.1 (A), P1.1, P1.2, P1.11, P1.12, P1.13, P1.14, P1.15, P1.16, P1.17, P2.1, Q1.2 (E), Q2.2 (E), R1.1, R3.1, TP1.1, U4.1 (GND); also elsewhere on the board
ISP_UC_CTL: Q2.3 (C); also elsewhere on the board
LED_OVFL1: P1.4, R5.2
LED_OVFL2: P1.6, R6.2
LED_OVFL3: P1.19, R7.2
LED_OVFL4: P1.20, R8.2
NTC_TEMP: P1.18; also elsewhere on the board
unnamed: D2.2 (K), Q2.1 (B), R3.2, R4.2
unnamed: LED3.2 (K), R5.1
unnamed: LED4.2 (K), R6.1
unnamed: LED5.2 (K), R7.1
unnamed: LED6.2 (K), R8.1
unnamed: P1.7, R13.2
unnamed: P1.8, R14.2
unnamed: P1.9, R9.2
unnamed: P1.10, R10.2
RESET_UC_CTL: Q1.3 (C); also elsewhere on the board
RESET_UC_EN: D1.2 (K), Q1.1 (B), R1.2, R2.2; also elsewhere on the board
RXD0_UI: R14.1; also elsewhere on the board
RXD3_CONSOLE: R10.1; also elsewhere on the board
TXD0_UI: R13.1; also elsewhere on the board
TXD3_CONSOLE: R9.1; also elsewhere on the board
UC_ISP_MODE_ENABLE: P1.3, R4.1
UC_RESET_CONTROL: P1.5, R2.1

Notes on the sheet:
DATA CONNECTOR
POWER
ISP CIRCUIT
OVERFLOW LEDS
